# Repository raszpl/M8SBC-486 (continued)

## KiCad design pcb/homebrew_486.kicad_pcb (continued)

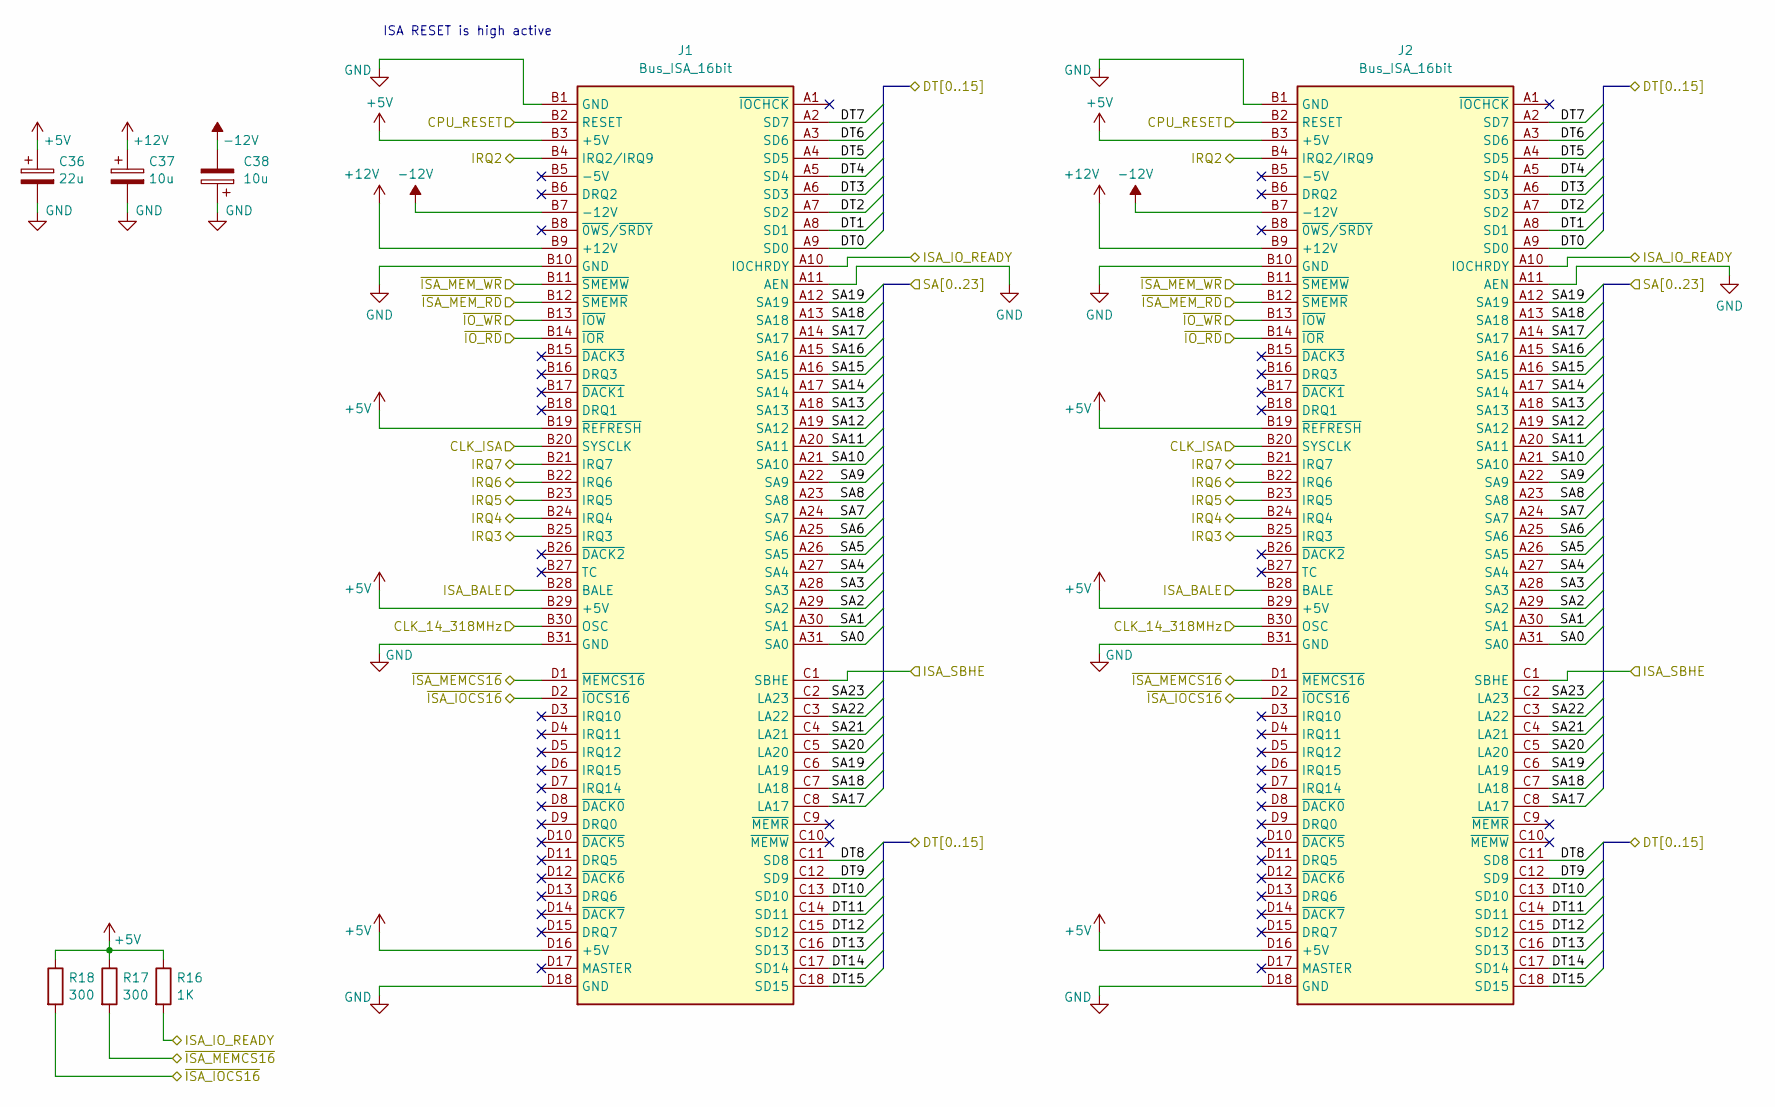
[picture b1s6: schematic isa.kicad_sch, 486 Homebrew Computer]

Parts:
C36: 22u; CP_Radial_D5.0mm_P2.50mm
C37, C38: 10u; CP_Radial_D5.0mm_P2.50mm
J1, J2: Bus_ISA_16bit; ISA16
R16: 1K; R_0805_2012Metric_Pad1.20x1.40mm_HandSolder
R17, R18: 300; R_0805_2012Metric_Pad1.20x1.40mm_HandSolder

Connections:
+5V: C36.1, J1.B3 (+5V), J1.B19 (~REFRESH), J1.B29 (+5V), J1.D16 (+5V), J2.B3 (+5V), J2.B19 (~REFRESH), J2.B29 (+5V), J2.D16 (+5V), R16.1, R17.1, R18.1; also elsewhere on the board
+12V: C37.1, J1.B9 (+12V), J2.B9 (+12V); also elsewhere on the board
-12V: C38.2, J1.B7 (-12V), J2.B7 (-12V); also elsewhere on the board
/CPU_RESET: J1.B2 (RESET), J2.B2 (RESET); also elsewhere on the board
/DT0: J1.A9 (SD0), J2.A9 (SD0); also elsewhere on the board
/DT1: J1.A8 (SD1), J2.A8 (SD1); also elsewhere on the board
/DT2: J1.A7 (SD2), J2.A7 (SD2); also elsewhere on the board
/DT3: J1.A6 (SD3), J2.A6 (SD3); also elsewhere on the board
/DT4: J1.A5 (SD4), J2.A5 (SD4); also elsewhere on the board
/DT5: J1.A4 (SD5), J2.A4 (SD5); also elsewhere on the board
/DT6: J1.A3 (SD6), J2.A3 (SD6); also elsewhere on the board
/DT7: J1.A2 (SD7), J2.A2 (SD7); also elsewhere on the board
/DT8: J1.C11 (SD8), J2.C11 (SD8); also elsewhere on the board
/DT9: J1.C12 (SD9), J2.C12 (SD9); also elsewhere on the board
/DT10: J1.C13 (SD10), J2.C13 (SD10); also elsewhere on the board
/DT11: J1.C14 (SD11), J2.C14 (SD11); also elsewhere on the board
/DT12: J1.C15 (SD12), J2.C15 (SD12); also elsewhere on the board
/DT13: J1.C16 (SD13), J2.C16 (SD13); also elsewhere on the board
/DT14: J1.C17 (SD14), J2.C17 (SD14); also elsewhere on the board
/DT15: J1.C18 (SD15), J2.C18 (SD15); also elsewhere on the board
/FPGA/CLK_14_318MHz: J1.B30 (OSC), J2.B30 (OSC); also elsewhere on the board
/FPGA/CLK_ISA: J1.B20 (SYSCLK), J2.B20 (SYSCLK); also elsewhere on the board
/FPGA/ISA_BALE: J1.B28 (BALE), J2.B28 (BALE); also elsewhere on the board
/FPGA/ISA_IO_READY: J1.A10 (IOCHRDY), J2.A10 (IOCHRDY), R16.2; also elsewhere on the board
/FPGA/ISA_SBHE: J1.C1 (SBHE), J2.C1 (SBHE); also elsewhere on the board
/FPGA/~IO_RD: J1.B14 (~IOR), J2.B14 (~IOR); also elsewhere on the board
/FPGA/~IO_WR: J1.B13 (~IOW), J2.B13 (~IOW); also elsewhere on the board
/FPGA/~ISA_IOCS16: J1.D2 (~IOCS16), J2.D2 (~IOCS16), R18.2; also elsewhere on the board
/FPGA/~ISA_MEMCS16: J1.D1 (~MEMCS16), J2.D1 (~MEMCS16), R17.2; also elsewhere on the board
/FPGA/~ISA_MEM_RD: J1.B12 (~SMEMR), J2.B12 (~SMEMR); also elsewhere on the board
/FPGA/~ISA_MEM_WR: J1.B11 (~SMEMW), J2.B11 (~SMEMW); also elsewhere on the board
/ISA/IRQ2: J1.B4 (IRQ2/IRQ9), J2.B4 (IRQ2/IRQ9); also elsewhere on the board
/ISA/IRQ3: J1.B25 (IRQ3), J2.B25 (IRQ3); also elsewhere on the board
/ISA/IRQ4: J1.B24 (IRQ4), J2.B24 (IRQ4); also elsewhere on the board
/ISA/IRQ5: J1.B23 (IRQ5), J2.B23 (IRQ5); also elsewhere on the board
/ISA/IRQ6: J1.B22 (IRQ6), J2.B22 (IRQ6); also elsewhere on the board
/ISA/IRQ7: J1.B21 (IRQ7), J2.B21 (IRQ7); also elsewhere on the board
/SA0: J1.A31 (SA0), J2.A31 (SA0); also elsewhere on the board
/SA1: J1.A30 (SA1), J2.A30 (SA1); also elsewhere on the board
/SA2: J1.A29 (SA2), J2.A29 (SA2); also elsewhere on the board
/SA3: J1.A28 (SA3), J2.A28 (SA3); also elsewhere on the board
/SA4: J1.A27 (SA4), J2.A27 (SA4); also elsewhere on the board
/SA5: J1.A26 (SA5), J2.A26 (SA5); also elsewhere on the board
/SA6: J1.A25 (SA6), J2.A25 (SA6); also elsewhere on the board
/SA7: J1.A24 (SA7), J2.A24 (SA7); also elsewhere on the board
/SA8: J1.A23 (SA8), J2.A23 (SA8); also elsewhere on the board
/SA9: J1.A22 (SA9), J2.A22 (SA9); also elsewhere on the board
/SA10: J1.A21 (SA10), J2.A21 (SA10); also elsewhere on the board
/SA11: J1.A20 (SA11), J2.A20 (SA11); also elsewhere on the board
/SA12: J1.A19 (SA12), J2.A19 (SA12); also elsewhere on the board
/SA13: J1.A18 (SA13), J2.A18 (SA13); also elsewhere on the board
/SA14: J1.A17 (SA14), J2.A17 (SA14); also elsewhere on the board
/SA15: J1.A16 (SA15), J2.A16 (SA15); also elsewhere on the board
/SA16: J1.A15 (SA16), J2.A15 (SA16); also elsewhere on the board
/SA17: J1.A14 (SA17), J1.C8 (LA17), J2.A14 (SA17), J2.C8 (LA17); also elsewhere on the board
/SA18: J1.A13 (SA18), J1.C7 (LA18), J2.A13 (SA18), J2.C7 (LA18); also elsewhere on the board
/SA19: J1.A12 (SA19), J1.C6 (LA19), J2.A12 (SA19), J2.C6 (LA19); also elsewhere on the board
/SA20: J1.C5 (LA20), J2.C5 (LA20); also elsewhere on the board
/SA21: J1.C4 (LA21), J2.C4 (LA21); also elsewhere on the board
/SA22: J1.C3 (LA22), J2.C3 (LA22); also elsewhere on the board
/SA23: J1.C2 (LA23), J2.C2 (LA23); also elsewhere on the board
GND: C36.2, C37.2, C38.1, J1.A11 (AEN), J1.B1 (GND), J1.B10 (GND), J1.B31 (GND), J1.D18 (GND), J2.A11 (AEN), J2.B1 (GND), J2.B10 (GND), J2.B31 (GND), J2.D18 (GND); also elsewhere on the board

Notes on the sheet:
ISA RESET is high active

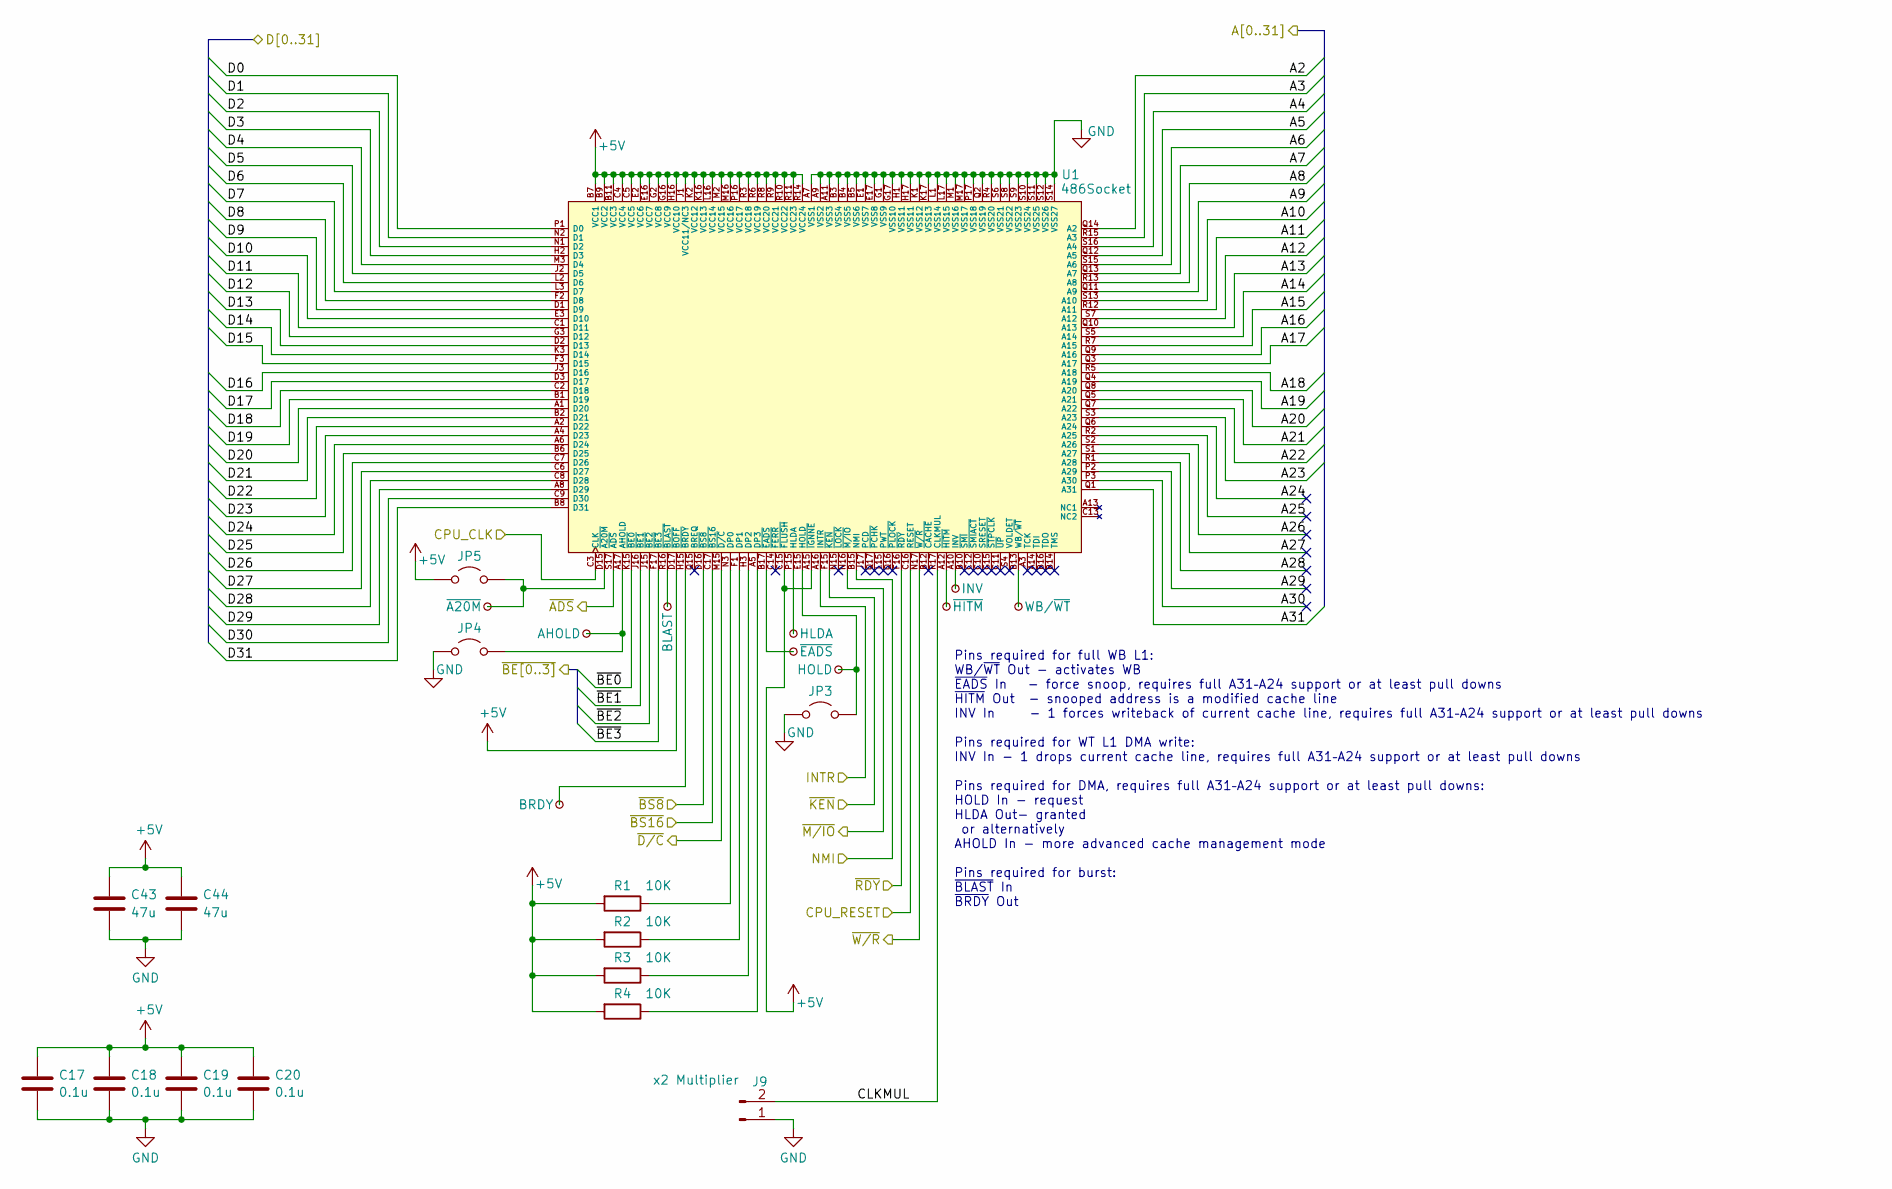
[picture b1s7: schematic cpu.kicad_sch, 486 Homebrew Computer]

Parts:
C17, C18, C19, C20: 0.1u; C_0805_2012Metric_Pad1.18x1.45mm_HandSolder
C43, C44: 47u; C_1210_3225Metric
J9: x2 Multiplier; PinHeader_1x02_P2.54mm_Vertical
JP3, JP4, JP5: Jumper_2_Open; SolderJumper-2_P1.3mm_Open_TrianglePad1.0x1.5mm
R1, R2, R3, R4: 10K; R_0805_2012Metric_Pad1.20x1.40mm_HandSolder
TP6: WB/~{WT}; TestPoint_Pad_D0.4mm
TP7: ~{HITM}; TestPoint_Pad_D0.4mm
TP8: HLDA; TestPoint_Pad_D0.4mm
TP9: HOLD; TestPoint_Pad_D0.4mm
TP10: INV; TestPoint_Pad_D0.4mm
TP11: ~{EADS}; TestPoint_Pad_D0.4mm
TP12: AHOLD; TestPoint_Pad_D0.4mm
TP13: BLAST; TestPoint_Pad_D0.4mm
TP14: BRDY; TestPoint_Pad_D0.4mm
TP15: ~{A20M}; TestPoint_Pad_D0.4mm
U1: 486Socket

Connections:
+5V: C17.2, C18.2, C19.2, C20.2, C43.2, C44.2, JP5.1 (A), R1.2, R2.2, R3.2, R4.2, U1.A15 (~IGNNE), U1.B7 (VCC1), U1.B9 (VCC2), U1.B11 (VCC3), U1.C4 (VCC4), U1.C5 (VCC5), U1.C15 (~FLUSH), U1.D17 (~BOFF), U1.E2 (VCC6), U1.E16 (VCC7), U1.G2 (VCC8), U1.G16 (VCC9), U1.H16 (VCC10), U1.J1 (VCC11/NC3), U1.K2 (VCC12), U1.K16 (VCC13), U1.L16 (VCC14), U1.M2 (VCC15), U1.M16 (VCC16), U1.P16 (VCC17), U1.R3 (VCC18), U1.R6 (VCC19), U1.R8 (VCC20), U1.R9 (VCC21), U1.R10 (VCC22), U1.R11 (VCC23), U1.R14 (VCC24); also elsewhere on the board
/A2: U1.Q14 (A2); also elsewhere on the board
/A3: U1.R15 (A3); also elsewhere on the board
/A4: U1.S16 (A4); also elsewhere on the board
/A5: U1.Q12 (A5); also elsewhere on the board
/A6: U1.S15 (A6); also elsewhere on the board
/A7: U1.Q13 (A7); also elsewhere on the board
/A8: U1.R13 (A8); also elsewhere on the board
/A9: U1.Q11 (A9); also elsewhere on the board
/A10: U1.S13 (A10); also elsewhere on the board
/A11: U1.R12 (A11); also elsewhere on the board
/A12: U1.S7 (A12); also elsewhere on the board
/A13: U1.Q10 (A13); also elsewhere on the board
/A14: U1.S5 (A14); also elsewhere on the board
/A15: U1.R7 (A15); also elsewhere on the board
/A16: U1.Q9 (A16); also elsewhere on the board
/A17: U1.Q3 (A17); also elsewhere on the board
/A18: U1.R5 (A18); also elsewhere on the board
/A19: U1.Q4 (A19); also elsewhere on the board
/A20: U1.Q8 (A20); also elsewhere on the board
/A21: U1.Q5 (A21); also elsewhere on the board
/A22: U1.Q7 (A22); also elsewhere on the board
/A23: U1.S3 (A23); also elsewhere on the board
/A24: U1.Q6 (A24)
/A25: U1.R2 (A25)
/A26: U1.S2 (A26)
/A27: U1.S1 (A27)
/A28: U1.R1 (A28)
/A29: U1.P2 (A29)
/A30: U1.P3 (A30)
/A31: U1.Q1 (A31); also elsewhere on the board
/CPU/CLKMUL: J9.2, U1.R17 (CLKMUL)
/CPU/CPU_CLK: U1.C3 (CLK); also elsewhere on the board
/CPU/NMI: U1.B15 (NMI); also elsewhere on the board
/CPU/~ADS: U1.S17 (~ADS); also elsewhere on the board
/CPU/~BE0: U1.K15 (~BE0); also elsewhere on the board
/CPU/~BE1: U1.J16 (~BE1); also elsewhere on the board
/CPU/~BE2: U1.J15 (~BE2); also elsewhere on the board
/CPU/~BE3: U1.F17 (~BE3); also elsewhere on the board
/CPU/~BS8: U1.D16 (~BS8); also elsewhere on the board
/CPU/~BS16: U1.C17 (~BS16); also elsewhere on the board
/CPU/~D/C: U1.M15 (~D/C); also elsewhere on the board
/CPU/~KEN: U1.F15 (~KEN); also elsewhere on the board
/CPU/~M/IO: U1.N16 (~M/IO); also elsewhere on the board
/CPU/~RDY: U1.F16 (~RDY); also elsewhere on the board
/CPU/~W/R: U1.N17 (~W/R); also elsewhere on the board
/CPU_RESET: U1.C16 (RESET); also elsewhere on the board
/D0: U1.P1 (D0); also elsewhere on the board
/D1: U1.N2 (D1); also elsewhere on the board
/D2: U1.N1 (D2); also elsewhere on the board
/D3: U1.H2 (D3); also elsewhere on the board
/D4: U1.M3 (D4); also elsewhere on the board
/D5: U1.J2 (D5); also elsewhere on the board
/D6: U1.L2 (D6); also elsewhere on the board
/D7: U1.L3 (D7); also elsewhere on the board
/D8: U1.F2 (D8); also elsewhere on the board
/D9: U1.D1 (D9); also elsewhere on the board
/D10: U1.E3 (D10); also elsewhere on the board
/D11: U1.C1 (D11); also elsewhere on the board
/D12: U1.G3 (D12); also elsewhere on the board
/D13: U1.D2 (D13); also elsewhere on the board
/D14: U1.K3 (D14); also elsewhere on the board
/D15: U1.F3 (D15); also elsewhere on the board
/D16: U1.J3 (D16); also elsewhere on the board
/D17: U1.D3 (D17); also elsewhere on the board
/D18: U1.C2 (D18); also elsewhere on the board
/D19: U1.B1 (D19); also elsewhere on the board
/D20: U1.A1 (D20); also elsewhere on the board
/D21: U1.B2 (D21); also elsewhere on the board
/D22: U1.A2 (D22); also elsewhere on the board
/D23: U1.A4 (D23); also elsewhere on the board
/D24: U1.A6 (D24); also elsewhere on the board
/D25: U1.B6 (D25); also elsewhere on the board
/D26: U1.C7 (D26); also elsewhere on the board
/D27: U1.C6 (D27); also elsewhere on the board
/D28: U1.C8 (D28); also elsewhere on the board
/D29: U1.A8 (D29); also elsewhere on the board
/D30: U1.C9 (D30); also elsewhere on the board
/D31: U1.B8 (D31); also elsewhere on the board
/INTR: U1.A16 (INTR); also elsewhere on the board
GND: C17.1, C18.1, C19.1, C20.1, C43.1, C44.1, J9.1, JP3.1 (A), JP4.1 (A), U1.A7 (VSS1), U1.A9 (VSS2), U1.A11 (VSS3), U1.B3 (VSS4), U1.B4 (VSS5), U1.B5 (VSS6), U1.E1 (VSS7), U1.E17 (VSS8), U1.G1 (VSS9), U1.G17 (VSS10), U1.H1 (VSS11), U1.H17 (VSS11), U1.K1 (VSS12), U1.K17 (VSS13), U1.L1 (VSS14), U1.L17 (VSS15), U1.M1 (VSS16), U1.M17 (VSS17), U1.P17 (VSS18), U1.Q2 (VSS19), U1.R4 (VSS20), U1.S6 (VSS21), U1.S8 (VSS22), U1.S9 (VSS23), U1.S10 (VSS24), U1.S11 (VSS25), U1.S12 (VSS26), U1.S14 (VSS27); also elsewhere on the board
unnamed: JP3.2 (B), TP9.1 (1_1), U1.E15 (HOLD)
unnamed: JP4.2 (B), TP12.1 (1_1), U1.A17 (AHOLD)
unnamed: JP5.2 (B), TP15.1 (1_1), U1.D15 (~A20M)
unnamed: R1.1, U1.N3 (DP0)
unnamed: R2.1, U1.F1 (DP1)
unnamed: R3.1, U1.H3 (DP2)
unnamed: R4.1, U1.A5 (DP3)
unnamed: TP8.1 (1_1), U1.P15 (HLDA)
unnamed: TP10.1 (1_1), U1.A10 (INV)
unnamed: TP6.1 (1_1), U1.B13 (WB/~WT)
unnamed: TP13.1 (1_1), U1.R16 (~BLAST)
unnamed: TP14.1 (1_1), U1.H15 (~BRDY)
unnamed: TP11.1 (1_1), U1.B17 (~EADS)
unnamed: TP7.1 (1_1), U1.A12 (~HITM)

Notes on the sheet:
Pins required for full WB L1: WB/~{WT} Out - activates WB ~{EADS} In - force snoop, requires full A31–A24 support or at least pull downs ~{HITM} Out - snooped address is a modified cache line INV In - 1 forces writeback of current cache line, requires full A31–A24 support or at least pull downs Pin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

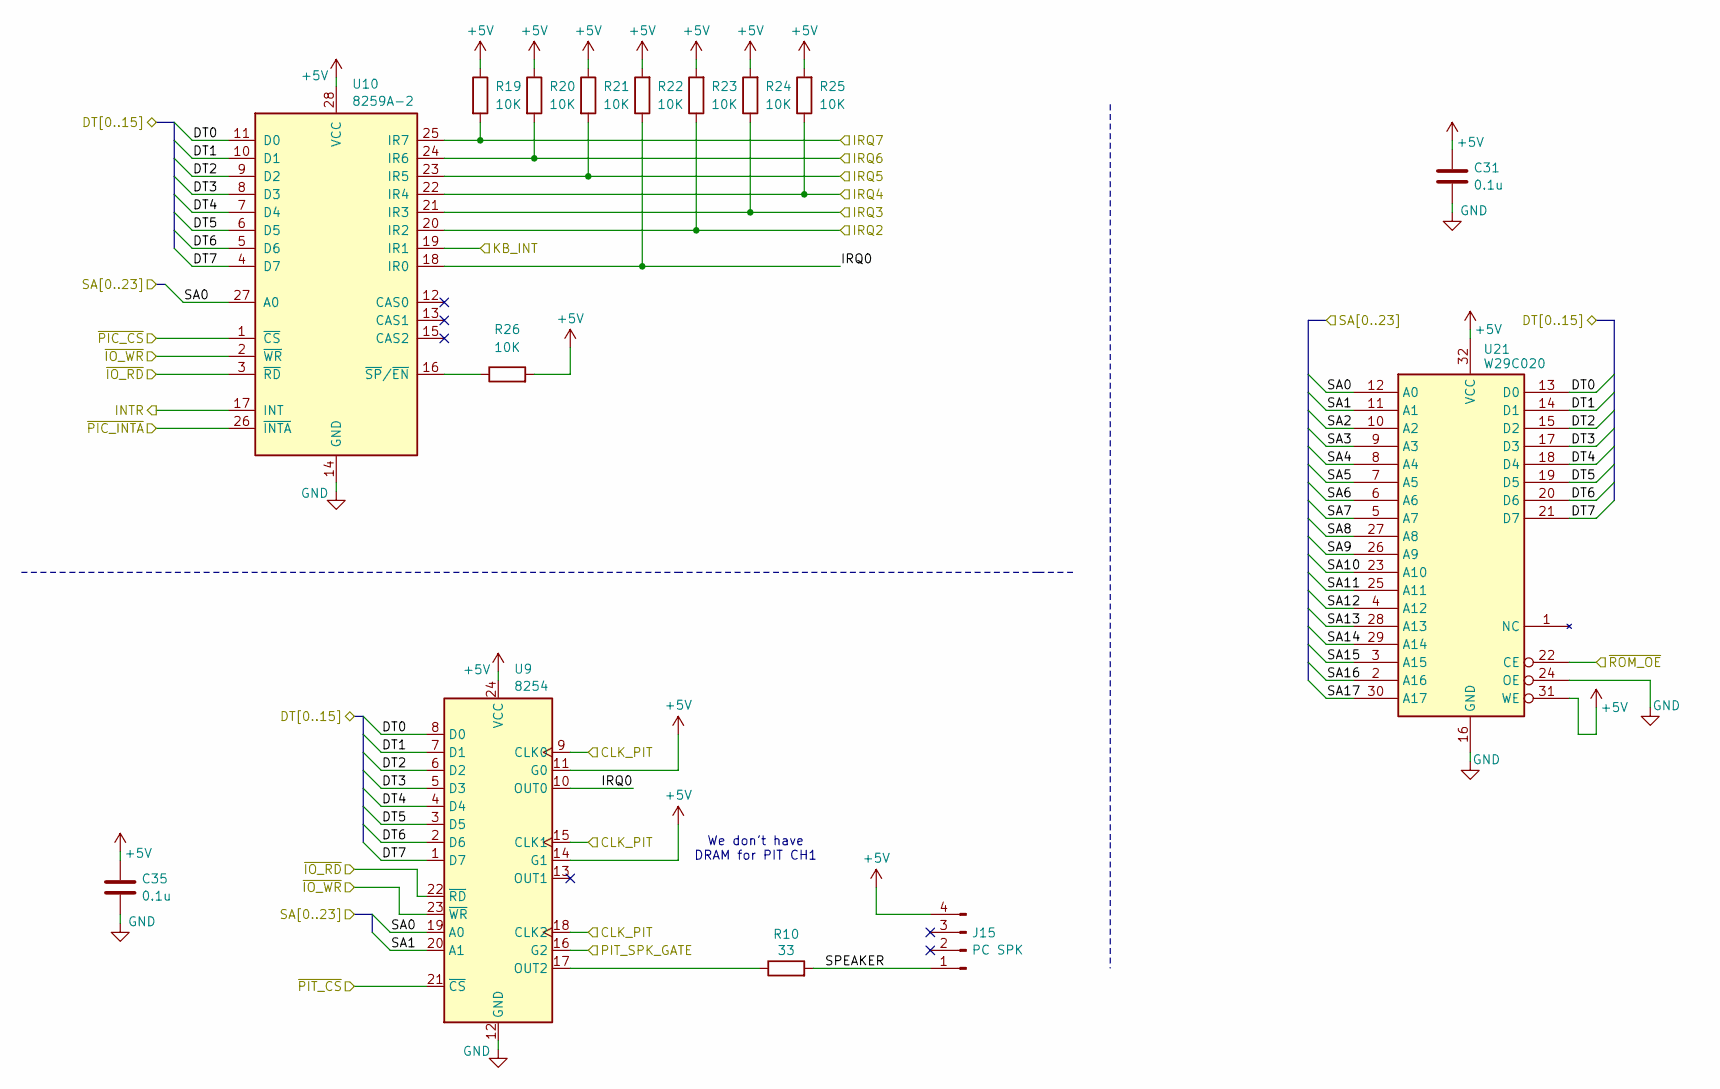
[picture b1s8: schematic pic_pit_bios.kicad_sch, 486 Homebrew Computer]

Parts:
C31, C35: 0.1u; C_0805_2012Metric_Pad1.18x1.45mm_HandSolder
J15: PC SPK; PinHeader_1x04_P2.54mm_Vertical
R10: 33; R_0805_2012Metric_Pad1.20x1.40mm_HandSolder
R19, R20, R21, R22, R23, R24, R25, R26: 10K; R_0805_2012Metric_Pad1.20x1.40mm_HandSolder
U9: 8254; DIP-24_W15.24mm
U10: 8259A-2; PLCC-28_THT-Socket
U21: W29C020; DIP-32_W15.24mm

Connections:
+5V: C31.2, C35.2, J15.4, R19.1, R20.1, R21.1, R22.2, R23.2, R24.2, R25.2, R26.2, U9.11 (G0), U9.14 (G1), U9.24 (VCC), U10.28 (VCC), U21.31 (WE), U21.32 (VCC); also elsewhere on the board
/CLK_PIT: U9.9 (CLK0), U9.15 (CLK1), U9.18 (CLK2); also elsewhere on the board
/DT0: U9.8 (D0), U10.11 (D0), U21.13 (D0); also elsewhere on the board
/DT1: U9.7 (D1), U10.10 (D1), U21.14 (D1); also elsewhere on the board
/DT2: U9.6 (D2), U10.9 (D2), U21.15 (D2); also elsewhere on the board
/DT3: U9.5 (D3), U10.8 (D3), U21.17 (D3); also elsewhere on the board
/DT4: U9.4 (D4), U10.7 (D4), U21.18 (D4); also elsewhere on the board
/DT5: U9.3 (D5), U10.6 (D5), U21.19 (D5); also elsewhere on the board
/DT6: U9.2 (D6), U10.5 (D6), U21.20 (D6); also elsewhere on the board
/DT7: U9.1 (D7), U10.4 (D7), U21.21 (D7); also elsewhere on the board
/FPGA/~IO_RD: U9.22 (~RD), U10.3 (~RD); also elsewhere on the board
/FPGA/~IO_WR: U9.23 (~WR), U10.2 (~WR); also elsewhere on the board
/INTR: U10.17 (INT); also elsewhere on the board
/ISA/IRQ2: R23.1, U10.20 (IR2); also elsewhere on the board
/ISA/IRQ3: R24.1, U10.21 (IR3); also elsewhere on the board
/ISA/IRQ4: R25.1, U10.22 (IR4); also elsewhere on the board
/ISA/IRQ5: R21.2, U10.23 (IR5); also elsewhere on the board
/ISA/IRQ6: R20.2, U10.24 (IR6); also elsewhere on the board
/ISA/IRQ7: R19.2, U10.25 (IR7); also elsewhere on the board
/KB_INT: U10.19 (IR1); also elsewhere on the board
/PIC, PIT, BIOS/IRQ0: R22.1, U9.10 (OUT0), U10.18 (IR0)
/PIC, PIT, BIOS/SPEAKER: J15.1, R10.2
/PIT_SPK_GATE: U9.16 (G2); also elsewhere on the board
/SA0: U9.19 (A0), U10.27 (A0), U21.12 (A0); also elsewhere on the board
/SA1: U9.20 (A1), U21.11 (A1); also elsewhere on the board
/SA2: U21.10 (A2); also elsewhere on the board
/SA3: U21.9 (A3); also elsewhere on the board
/SA4: U21.8 (A4); also elsewhere on the board
/SA5: U21.7 (A5); also elsewhere on the board
/SA6: U21.6 (A6); also elsewhere on the board
/SA7: U21.5 (A7); also elsewhere on the board
/SA8: U21.27 (A8); also elsewhere on the board
/SA9: U21.26 (A9); also elsewhere on the board
/SA10: U21.23 (A10); also elsewhere on the board
/SA11: U21.25 (A11); also elsewhere on the board
/SA12: U21.4 (A12); also elsewhere on the board
/SA13: U21.28 (A13); also elsewhere on the board
/SA14: U21.29 (A14); also elsewhere on the board
/SA15: U21.3 (A15); also elsewhere on the board
/SA16: U21.2 (A16); also elsewhere on the board
/SA17: U21.30 (A17); also elsewhere on the board
/~PIC_CS: U10.1 (~CS); also elsewhere on the board
/~PIC_INTA: U10.26 (~INTA); also elsewhere on the board
/~PIT_CS: U9.21 (~CS); also elsewhere on the board
/~ROM_OE: U21.22 (CE); also elsewhere on the board
GND: C31.1, C35.1, U9.12 (GND), U10.14 (GND), U21.16 (GND), U21.24 (OE); also elsewhere on the board
unnamed: R10.1, U9.17 (OUT2)
unnamed: R26.1, U10.16 (~SP/~EN)

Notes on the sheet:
We don't have DRAM for PIT CH1

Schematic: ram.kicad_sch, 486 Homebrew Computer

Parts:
C23, C24, C25, C26, C27, C28, C29, C30: 0.1u; C_0805_2012Metric_Pad1.18x1.45mm_HandSolder
U11, U12, U13, U14, U15, U16, U17, U18: HM628512; SOP-32_11.305x20.495mm_P1.27mm

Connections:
+5V: C23.2, C24.2, C25.2, C26.2, C27.2, C28.2, C29.2, C30.2, U11.32 (VCC), U12.32 (VCC), U13.32 (VCC), U14.32 (VCC), U15.32 (VCC), U16.32 (VCC), U17.32 (VCC), U18.32 (VCC); also elsewhere on the board
/A2: U11.12 (A0), U12.12 (A0), U13.12 (A0), U14.12 (A0), U15.12 (A0), U16.12 (A0), U17.12 (A0), U18.12 (A0); also elsewhere on the board
/A3: U11.11 (A1), U12.11 (A1), U13.11 (A1), U14.11 (A1), U15.11 (A1), U16.11 (A1), U17.11 (A1), U18.11 (A1); also elsewhere on the board
/A4: U11.10 (A2), U12.10 (A2), U13.10 (A2), U14.10 (A2), U15.10 (A2), U16.10 (A2), U17.10 (A2), U18.10 (A2); also elsewhere on the board
/A5: U11.9 (A3), U12.9 (A3), U13.9 (A3), U14.9 (A3), U15.9 (A3), U16.9 (A3), U17.9 (A3), U18.9 (A3); also elsewhere on the board
/A6: U11.8 (A4), U12.8 (A4), U13.8 (A4), U14.8 (A4), U15.8 (A4), U16.8 (A4), U17.8 (A4), U18.8 (A4); also elsewhere on the board
/A7: U11.7 (A5), U12.7 (A5), U13.7 (A5), U14.7 (A5), U15.7 (A5), U16.7 (A5), U17.7 (A5), U18.7 (A5); also elsewhere on the board
/A8: U11.6 (A6), U12.6 (A6), U13.6 (A6), U14.6 (A6), U15.6 (A6), U16.6 (A6), U17.6 (A6), U18.6 (A6); also elsewhere on the board
/A9: U11.5 (A7), U12.5 (A7), U13.5 (A7), U14.5 (A7), U15.5 (A7), U16.5 (A7), U17.5 (A7), U18.5 (A7); also elsewhere on the board
/A10: U11.27 (A8), U12.27 (A8), U13.27 (A8), U14.27 (A8), U15.27 (A8), U16.27 (A8), U17.27 (A8), U18.27 (A8); also elsewhere on the board
/A11: U11.26 (A9), U12.26 (A9), U13.26 (A9), U14.26 (A9), U15.26 (A9), U16.26 (A9), U17.26 (A9), U18.26 (A9); also elsewhere on the board
/A12: U11.23 (A10), U12.23 (A10), U13.23 (A10), U14.23 (A10), U15.23 (A10), U16.23 (A10), U17.23 (A10), U18.23 (A10); also elsewhere on the board
/A13: U11.25 (A11), U12.25 (A11), U13.25 (A11), U14.25 (A11), U15.25 (A11), U16.25 (A11), U17.25 (A11), U18.25 (A11); also elsewhere on the board
/A14: U11.4 (A12), U12.4 (A12), U13.4 (A12), U14.4 (A12), U15.4 (A12), U16.4 (A12), U17.4 (A12), U18.4 (A12); also elsewhere on the board
/A15: U11.28 (A13), U12.28 (A13), U13.28 (A13), U14.28 (A13), U15.28 (A13), U16.28 (A13), U17.28 (A13), U18.28 (A13); also elsewhere on the board
/A16: U11.3 (A14), U12.3 (A14), U13.3 (A14), U14.3 (A14), U15.3 (A14), U16.3 (A14), U17.3 (A14), U18.3 (A14); also elsewhere on the board
/A17: U11.31 (A15), U12.31 (A15), U13.31 (A15), U14.31 (A15), U15.31 (A15), U16.31 (A15), U17.31 (A15), U18.31 (A15); also elsewhere on the board
/A18: U11.2 (A16), U12.2 (A16), U13.2 (A16), U14.2 (A16), U15.2 (A16), U16.2 (A16), U17.2 (A16), U18.2 (A16); also elsewhere on the board
/A19: U11.30 (A17), U12.30 (A17), U13.30 (A17), U14.30 (A17), U15.30 (A17), U16.30 (A17), U17.30 (A17), U18.30 (A17); also elsewhere on the board
/A20: U11.1 (A18), U12.1 (A18), U13.1 (A18), U14.1 (A18), U15.1 (A18), U16.1 (A18), U17.1 (A18), U18.1 (A18); also elsewhere on the board
/D0: U11.13 (Q0), U15.13 (Q0); also elsewhere on the board
/D1: U11.14 (Q1), U15.14 (Q1); also elsewhere on the board
/D2: U11.15 (Q2), U15.15 (Q2); also elsewhere on the board
/D3: U11.17 (Q3), U15.17 (Q3); also elsewhere on the board
/D4: U11.18 (Q4), U15.18 (Q4); also elsewhere on the board
/D5: U11.19 (Q5), U15.19 (Q5); also elsewhere on the board
/D6: U11.20 (Q6), U15.20 (Q6); also elsewhere on the board
/D7: U11.21 (Q7), U15.21 (Q7); also elsewhere on the board
/D8: U12.13 (Q0), U16.13 (Q0); also elsewhere on the board
/D9: U12.14 (Q1), U16.14 (Q1); also elsewhere on the board
/D10: U12.15 (Q2), U16.15 (Q2); also elsewhere on the board
/D11: U12.17 (Q3), U16.17 (Q3); also elsewhere on the board
/D12: U12.18 (Q4), U16.18 (Q4); also elsewhere on the board
/D13: U12.19 (Q5), U16.19 (Q5); also elsewhere on the board
/D14: U12.20 (Q6), U16.20 (Q6); also elsewhere on the board
/D15: U12.21 (Q7), U16.21 (Q7); also elsewhere on the board
/D16: U13.21 (Q7), U17.21 (Q7); also elsewhere on the board
/D17: U13.13 (Q0), U17.13 (Q0); also elsewhere on the board
/D18: U13.20 (Q6), U17.20 (Q6); also elsewhere on the board
/D19: U13.14 (Q1), U17.14 (Q1); also elsewhere on the board
/D20: U13.19 (Q5), U17.19 (Q5); also elsewhere on the board
/D21: U13.15 (Q2), U17.15 (Q2); also elsewhere on the board
/D22: U13.18 (Q4), U17.18 (Q4); also elsewhere on the board
/D23: U13.17 (Q3), U17.17 (Q3); also elsewhere on the board
/D24: U14.21 (Q7), U18.21 (Q7); also elsewhere on the board
/D25: U14.13 (Q0), U18.13 (Q0); also elsewhere on the board
/D26: U14.20 (Q6), U18.20 (Q6); also elsewhere on the board
/D27: U14.14 (Q1), U18.14 (Q1); also elsewhere on the board
/D28: U14.19 (Q5), U18.19 (Q5); also elsewhere on the board
/D29: U14.15 (Q2), U18.15 (Q2); also elsewhere on the board
/D30: U14.18 (Q4), U18.18 (Q4); also elsewhere on the board
/D31: U14.17 (Q3), U18.17 (Q3); also elsewhere on the board
/FPGA/~RAM_OE_B0: U11.24 (~OE), U15.24 (~OE); also elsewhere on the board
/FPGA/~RAM_OE_B1: U12.24 (~OE), U16.24 (~OE); also elsewhere on the board
/FPGA/~RAM_OE_B2: U13.24 (~OE), U17.24 (~OE); also elsewhere on the board
/FPGA/~RAM_OE_B3: U14.24 (~OE), U18.24 (~OE); also elsewhere on the board
/FPGA/~RAM_WE_B0: U11.29 (~WE), U15.29 (~WE); also elsewhere on the board
/FPGA/~RAM_WE_B1: U12.29 (~WE), U16.29 (~WE); also elsewhere on the board
/FPGA/~RAM_WE_B2: U13.29 (~WE), U17.29 (~WE); also elsewhere on the board
/FPGA/~RAM_WE_B3: U14.29 (~WE), U18.29 (~WE); also elsewhere on the board
/~RAM_CS0: U11.22 (~CS), U12.22 (~CS), U13.22 (~CS), U14.22 (~CS); also elsewhere on the board
/~RAM_CS1: U15.22 (~CS), U16.22 (~CS), U17.22 (~CS), U18.22 (~CS); also elsewhere on the board
GND: C23.1, C24.1, C25.1, C26.1, C27.1, C28.1, C29.1, C30.1, U11.16 (GND), U12.16 (GND), U13.16 (GND), U14.16 (GND), U15.16 (GND), U16.16 (GND), U17.16 (GND), U18.16 (GND); also elsewhere on the board

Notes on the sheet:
16-23
First 2MB
00-07
24-31
08-15
Last 2MB

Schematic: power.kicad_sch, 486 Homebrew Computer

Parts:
C1, C2, C39: 22u; CP_Radial_D5.0mm_P2.50mm
C3, C4: 0.1u; C_0805_2012Metric_Pad1.18x1.45mm_HandSolder
D1: PWR_LED; LED_D4.0mm
J3: ATX-20; Molex_Mini-Fit_Jr_5566-20A_2x10_P4.20mm_Vertical
J19, J20, J21, J22: Conn_01x02_Pin; PinHeader_1x02_P2.54mm_Vertical
JP2: ATX power; Fuse_1210_3225Metric; not fitted
R5, R6, R7: 120; R_0805_2012Metric_Pad1.20x1.40mm_HandSolder
R8: 200; R_0805_2012Metric_Pad1.20x1.40mm_HandSolder
R14: 1K; R_0805_2012Metric_Pad1.20x1.40mm_HandSolder
SW1: SW_SPDT; PinHeader_1x03_P2.54mm_Vertical
U3, U4: AMS1117; SOT-223-3_TabPin2

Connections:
+2V5: C1.1, R5.1, U4.2 (VO); also elsewhere on the board
+3.3V: C2.1, JP2.1 (A), R7.1, U3.2 (VO); also elsewhere on the board
+3.3V_atx: J3.1 (+3.3V), J3.2 (+3.3V), J3.11 (+3.3V), JP2.2 (B)
+5V: C3.1, C4.1, C39.1, D1.2 (A), J3.4 (+5V), J3.6 (+5V), J3.19 (+5V), J3.20 (+5V), U3.3 (VI), U4.3 (VI); also elsewhere on the board
+12V: J3.10 (+12V); also elsewhere on the board
-12V: J3.12 (-12V); also elsewhere on the board
GND: C1.2, C2.2, C3.2, C4.2, C39.2, J3.3 (GND), J3.5 (GND), J3.7 (GND), J3.13 (GND), J3.15 (GND), J3.16 (GND), J3.17 (GND), J19.1, J19.2, J20.1, J20.2, J21.1, J21.2, J22.1, J22.2, R6.1, R8.1, R14.2, SW1.3 (C); also elsewhere on the board
unnamed: D1.1 (K), R14.1
unnamed: J3.14 (PS_ON#), SW1.2 (B)
unnamed: R7.2, R8.2, U3.1 (ADJ)
unnamed: R5.2, R6.2, U4.1 (ADJ)

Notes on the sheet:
Populate either U3 or JP2

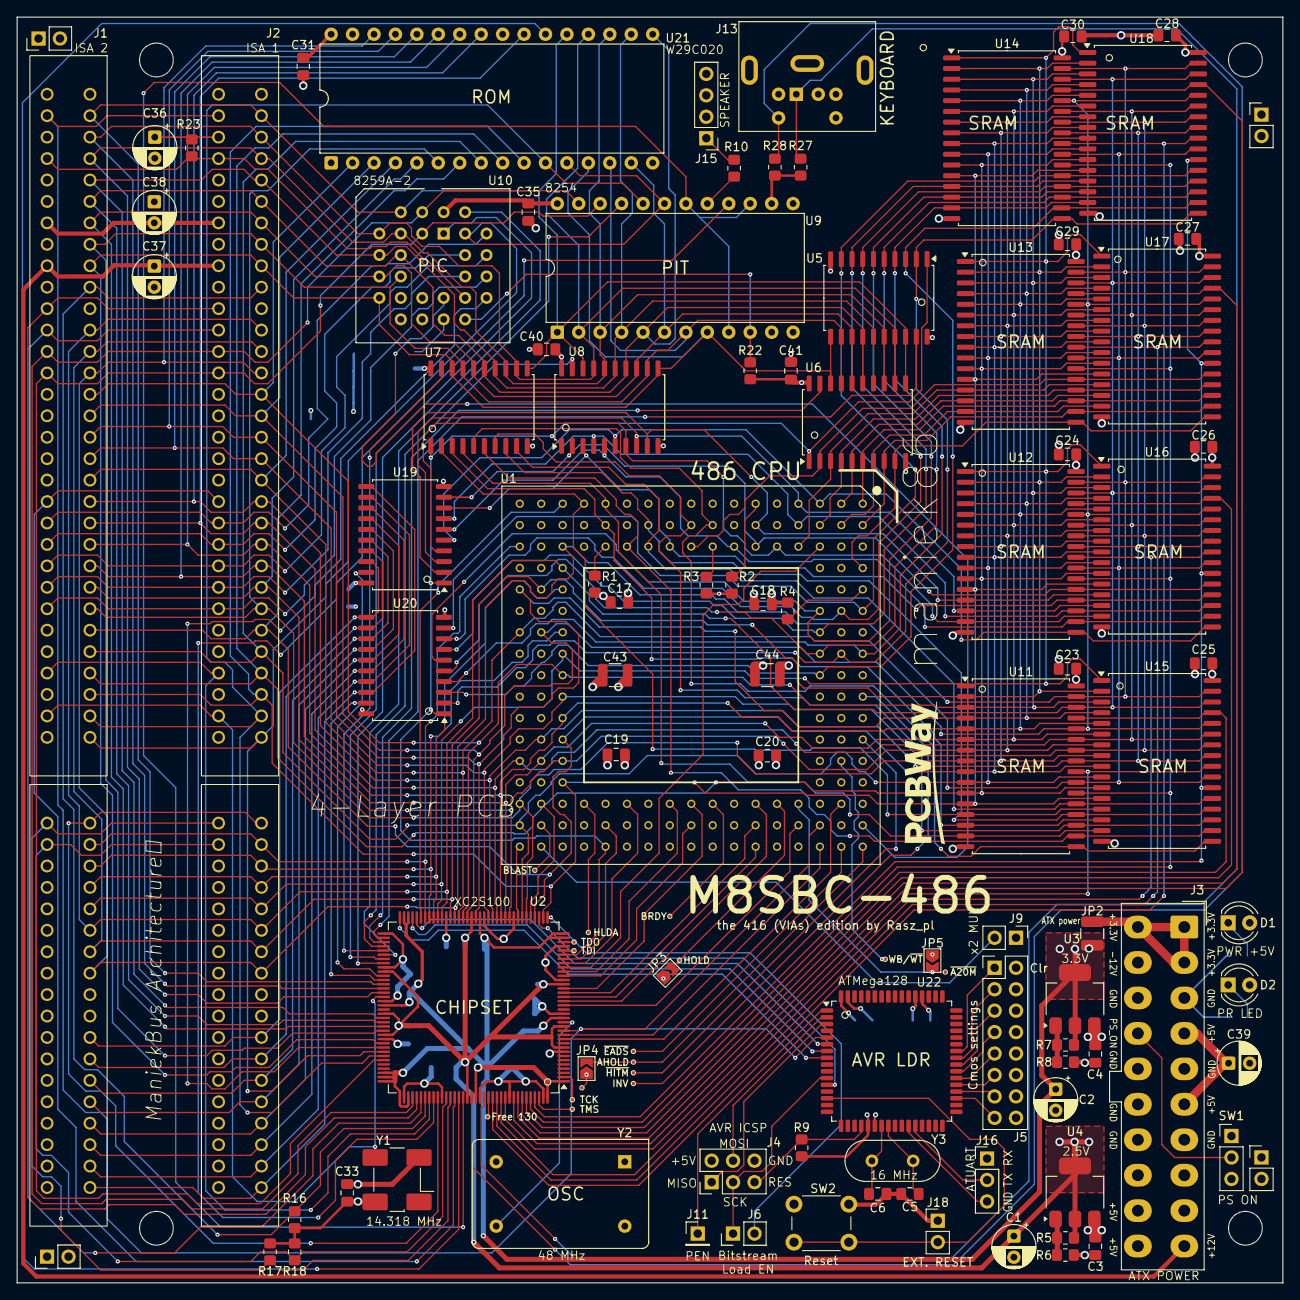
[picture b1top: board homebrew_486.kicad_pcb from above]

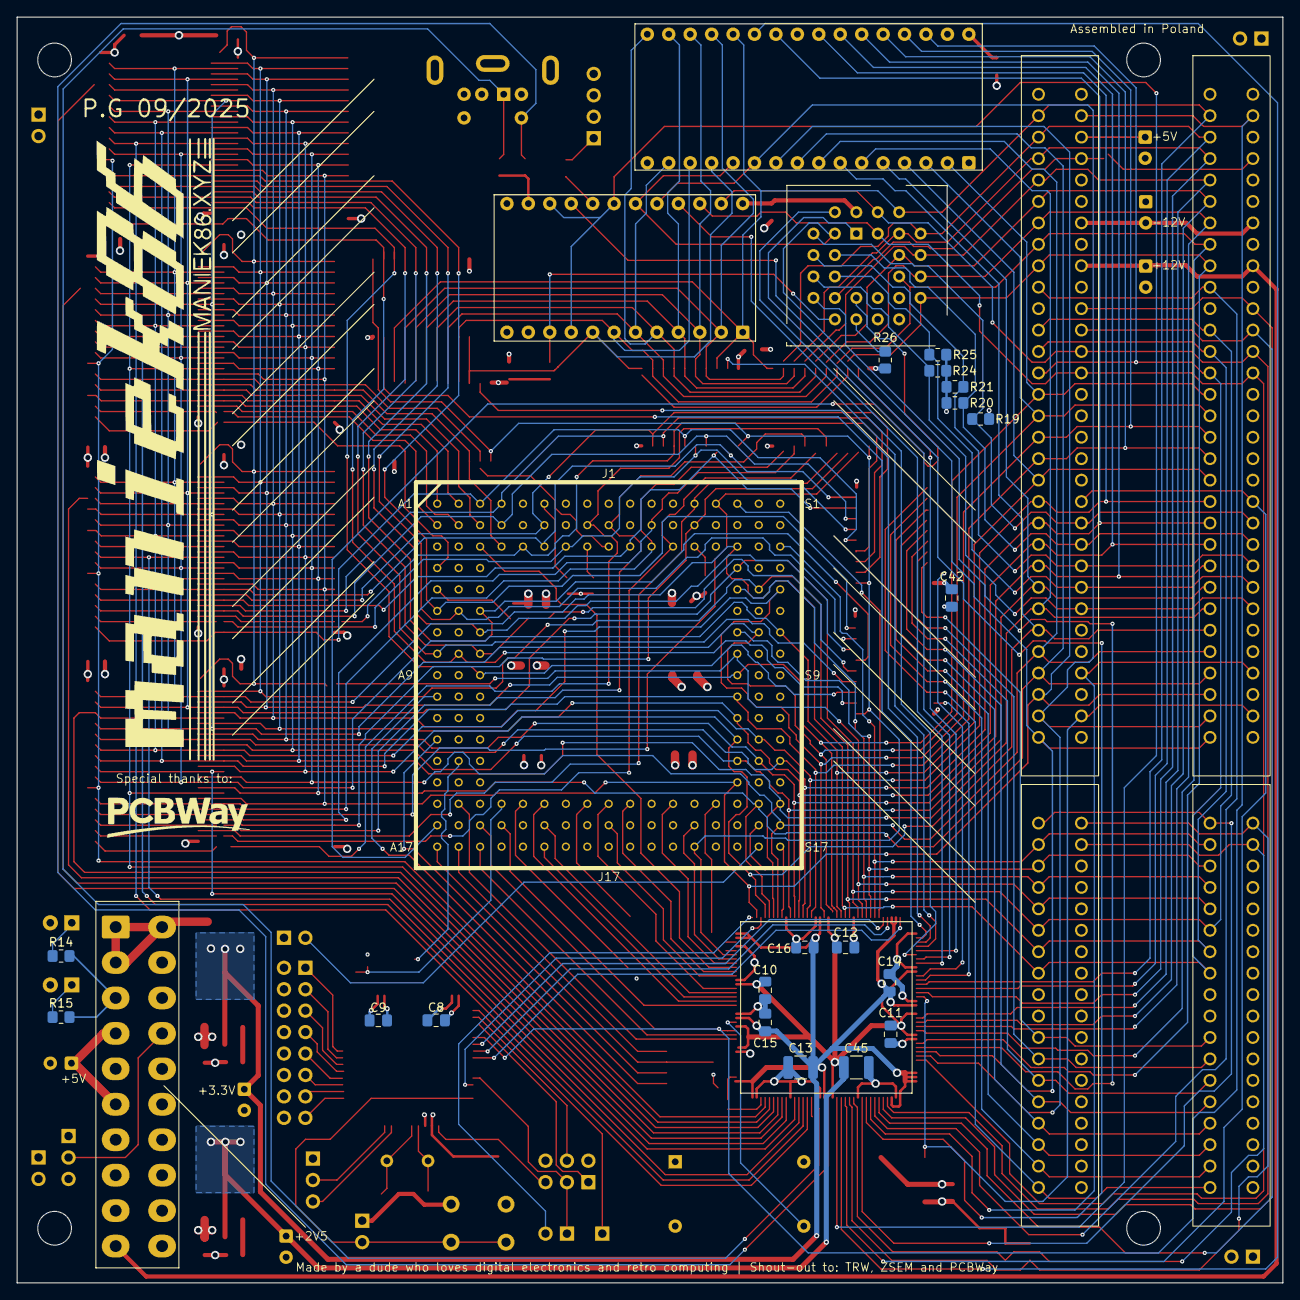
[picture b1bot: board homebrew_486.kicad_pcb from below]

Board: 4 copper layers, 150.0 x 150.0 mm, 156 parts (41 on the bottom side), 213 nets.
